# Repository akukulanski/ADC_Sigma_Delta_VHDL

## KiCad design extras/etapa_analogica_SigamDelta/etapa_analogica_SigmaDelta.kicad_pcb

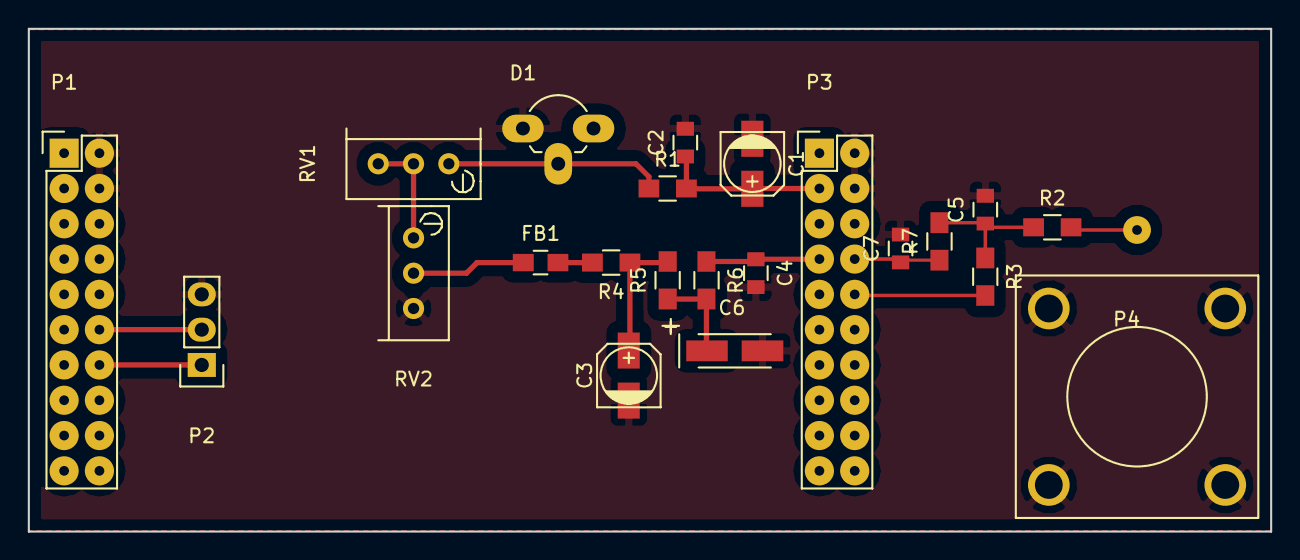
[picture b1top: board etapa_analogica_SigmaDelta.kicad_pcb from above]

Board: 2 copper layers, 89.4 x 36.2 mm, 22 parts (0 on the bottom side), 16 nets.

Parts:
C1, C3: 10u; c_elec_4x5.7
C2: 0,01u; C_0805
C4: 10u; C_0805
C5, C7: .1n; C_0805
C6: 10u; TantalC_SizeA_EIA-3216_HandSoldering
D1: LM336; TO-92_Rugged_Reverse
FB1: FILTER; C_0805_HandSoldering
P1, P3: CONN_02X10; Pin_Header_Straight_2x10
P2: CONN_01X03; Pin_Header_Straight_1x03
P4: BNC; chasis_bnc
R1: 560; R_0805_HandSoldering
R2, R3, R7: 150k; R_0805_HandSoldering
R4, R5, R6: 15k; R_0805_HandSoldering
RV1: 100; Potentiometer_Bourns_3296W_3-8Zoll_Inline_ScrewUp
RV2: 10k; Potentiometer_Bourns_3296W_3-8Zoll_Inline_ScrewUp

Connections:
/3,3v: C1.1, C2.1, P1.3, P3.3, R1.2
/5v: P1.1, P3.1
/N40: C4.1, P3.7, R6.1
/P35: P3.10, R3.2
/P41: C7.1, P3.8, R7.1
/Rx: P1.14, P2.1
/Tx: P1.12, P2.2
GND: C1.2, C2.2, C3.2, C4.2, C5.2, C6.2, C7.2, D1.1, P1.2, P1.4, P2.3, P3.2, P3.4, P4.2, RV2.3
unnamed: C3.1, R4.1, R5.2
unnamed: C5.1, R2.1, R3.1, R7.2
unnamed: C6.1, R5.1, R6.2
unnamed: D1.2, R1.1, RV1.1
unnamed: FB1.1, RV2.2
unnamed: FB1.2, R4.2
unnamed: P4.1, R2.2
unnamed: RV1.2, RV1.3, RV2.1

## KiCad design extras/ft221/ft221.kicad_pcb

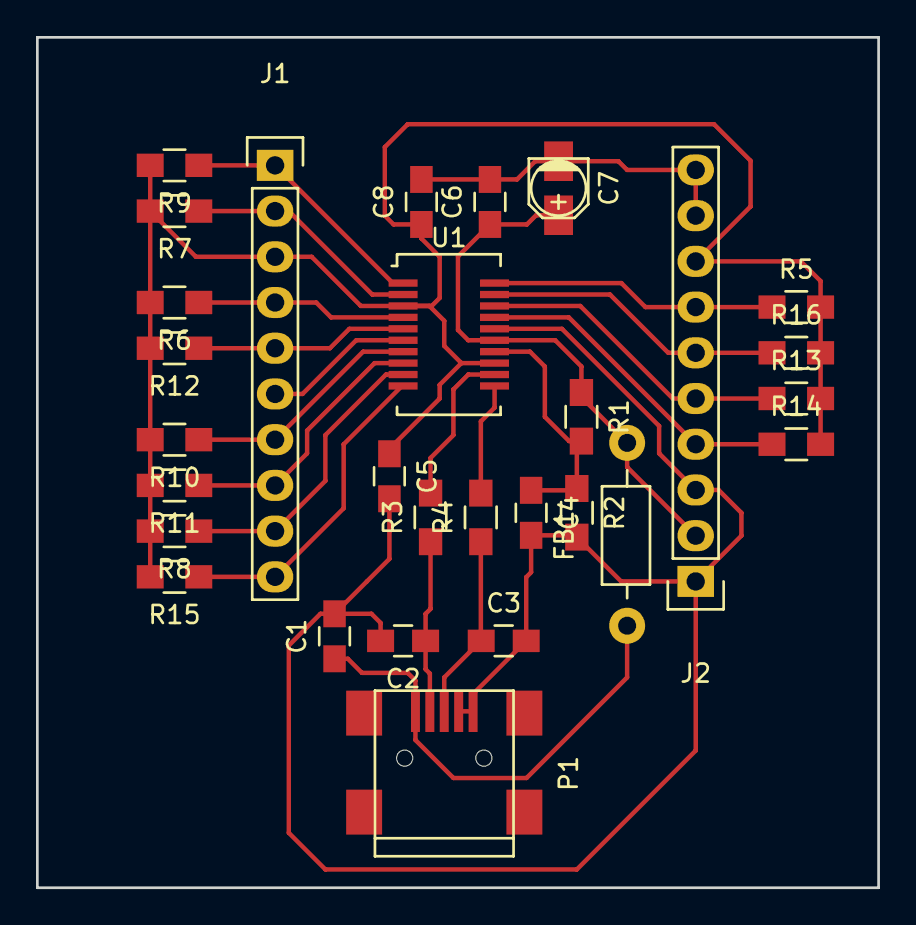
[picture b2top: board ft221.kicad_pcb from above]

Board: 2 copper layers, 46.7 x 47.2 mm, 29 parts (0 on the bottom side), 21 nets.

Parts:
C1, C4: 10n; C_0805_HandSoldering
C2, C3: 47p; C_0805_HandSoldering
C5, C6, C8: 0.1u; C_0805_HandSoldering
C7: 47u; c_elec_3x5.3
FB1: FILTER; Choke_Horizontal_RM10mm
J1, J2: SIL10; Pin_Header_Straight_1x10
P1: USB_B; USB_Mini-B
R1: 10k; R_0805_HandSoldering
R2: 15k; R_0805_HandSoldering
R3, R4: 27; R_0805_HandSoldering
R5, R6, R7, R8, R9, R10, R11, R12, R13, R14, R15, R16: 47k; R_0805_HandSoldering
U1: FT221; SSOP-20_5.99x8.66mm_Pitch0.635mm

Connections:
/CBUS3: J2.6, R16.1, U1.19
/CLK: J2.5, R13.1, U1.18
/CS#: J2.4, R14.1, U1.17
/IO0: J2.7, R5.1, U1.20
/IO1: J1.4, R6.1, U1.4
/IO2: J1.2, R7.1, U1.2
/IO3: J1.9, R8.1, U1.9
/IO4: J1.1, R9.1, U1.1
/IO5: J1.7, R10.1, U1.7
/IO6: J1.8, R11.1, U1.8
/IO7: J1.5, R12.1, U1.5
/MISO: J1.10, R15.1, U1.10
/VCCIO: C5.1, C8.1, J1.3, J2.8, R5.2, R6.2, R7.2, R8.2, R9.2, R10.2, R11.2, R12.2, R13.2, R14.2, R15.2, R16.2, U1.3, U1.13
GND: C1.2, C2.2, C3.2, C4.2, C5.2, C6.2, C7.2, C8.2, J1.6, J2.1, J2.3, J2.9, J2.10, P1.4, P1.5, R2.2, U1.6, U1.16
unnamed: C1.1, FB1.1, P1.1
unnamed: C2.1, P1.2, R3.1
unnamed: C3.1, P1.3, R4.1
unnamed: C4.1, R1.2, R2.1, U1.14
unnamed: R3.2, U1.12
unnamed: R4.2, U1.11
VCC: C6.1, C7.1, FB1.2, J2.2, R1.1, U1.15

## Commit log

2015-07-20 Commit inicial.
2015-07-21 Subiendo cic.vhd (falta bloque decimator y probar).
2015-07-21 Correcciones en el cic. Bloque decimador y su TB. Falta bufferear con F-F y TB del cic.
    Agregada funciton vectorize, para convertir
    std_logic a vector(0 downto 0)
    y no perder tiempo agregando signals.
2015-07-21 Buffereado con F-F los acumuladores a la salida, y los comb a la ent.
2015-07-21 Corregido los errores que mostraba la sintesis. Mirar los warnings.
2015-07-22 Subido archivos configuracion proyecto. Modificado cic (puesta a 0 señales no usadas) Puesto formato a los archivos.
2015-07-22 Corregido los truncamientos en cic. Falta un testbench completo.
2015-07-22 Combs, pasado a registrar la salida en vez de la entrada.
2015-07-23 Se agregan delayline y mac con preadder. No fueron probados. (igual no creo que esten mal, yo no tengo errores ajajaj)
2015-07-23 Se conecto output en preadd_mac
2015-07-23 Modificacion en RAM - Escritura en un ciclo de clock
2015-07-24 Test bench para ram. Cambiado nombre entity 'delay line' a 'ram'.
2015-07-24 Se agregan TB y fuentes de la generacion de punteros de ram. Se actualiza preaddmac para su correcto funcionamiento. DelayLine no funciona. Falta filtro FIR. Kuku se la come
2015-07-24 empezado el fir. modificación de ca2 previa a ram para multiplicación
2015-07-25 Cambiado todos los "add" que significaban "address" por "addr" para no confundir con las sumas.
2015-07-25 cambiando cosas
2015-07-25 Corregido address generator. Decrementa el contador 'cnt' en vez de incrementar.
2015-07-26 fir tb_ok.. revisar
2015-07-26 Se agrega testbench del CIC utilizando archivos (input stream de bits generado por Matlab)
2015-07-26 corregidas un par de cosas
2015-07-26 unificando2
2015-07-26 Corregida la ram. El multiplexor va ahí. Leer los comentarios. Implementado en block ram pero se lo cambia facil a distributed ram con un attribute (leer los comentarios!!!!!)
2015-07-26 Solucionado quilombo con push simultaneos mismo archivo.
2015-07-26 Ahi quedo corregido ram.vhd con los cambios antes mencionados
2015-07-26 un cambio chico en el fir
2015-07-26 Agregado dos generics para extender en signo y que reconozca el bloque mac con preadder dentro de un dsp. Los F-F de entrada se los puede llegar a sacar (igual los implementa dentro del dsp).
2015-07-26 cambio chico en fir y address_generator
2015-07-26 incorporación de cambios en mac al fir
2015-07-27 CIC corregido (decimador) - testbench anda ok! (sólo falta probar recortando bits :D)
2015-07-27 Cambiado decimator a algo que hace lo mismo pero escrito de mejor forma. Cambios menores: Sacado todas las tildes. Cambiado las ñ por n. Cambiados los integer por natural cuando eran anchos palabra.
2015-07-27 corrección en decimador
2015-07-27 eliminado el estado superfluo writing del address generator
2015-07-27 sacadas un par de líneas innecesarias
2015-07-27 agrego los scripts de vhdl
2015-07-27 Subido un package con los coeficientes. Hechas las modificaciones necesarias en el fir.
2015-07-28 Corregido scrip matlab,package y fir.
2015-07-28 Probado el fir. Correcciones menores hechas: - Cambiado (N_coeffs-1 downto 0) por (0 to N_coeffs-1) en coefficients.vhd - Agregada FF en lectura ROM(que esta dentro de la block-ram en realidad) para 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
2015-07-28 Sacados los when enable_mac_new_input = '1' else (others => '0') y extendido enable_mac_new_input hasta que se genere la salida. Conctado enable_mac_new_input a ce del preadd_mac.
2015-07-28 decimador sin retraso. renombro Coefficients.vhd por my_coeffs.vhd
2015-07-28 Ejemplo de lvds para instanciar en el top level
2015-07-28 Agrego archivos para comunicación serie
2015-07-29 Se agrega: - UART - Ejemplo de pll - top_level (solo del adc) - ad_uart (top_level + UART )
    Se mueve mytypes_pkg del archivo cic hacia la carpeta general CIC
2015-07-29 Verificado la respuesta al escalon fir con matlab (a mano, no exporte a archivo, sino compare valores).
2015-07-30 Cambios organiaztivos. Se cambia la esctructura de carpetas y se agrega un archivos de constantes. Quedan por cambiar algunas constantes de unos archivos todavia.
2015-07-30 Cambios menores
2015-07-30 programa para recibir por pto serie-OK!
2015-07-30 Separado totalmente las constantes del test_bench y de sintesis. Para esto agregado generic IS_TB y funciones decision. Para el futuro podriamos, calcular bits de cada etapa del cic en una funcion, y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
2015-07-30 Se agrega adc_uart.ucf
2015-09-03 Se modifico el CIC para que tenga logica de saturación positiva (no llegue al 100...000) y se hizo un testbench mediocre para probar su totalidad. Habria que hacer un TB mejor que exporte a matlab. E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
2015-09-08 Added: Synthesis, Place&Route and bitstreaming generator with makefile.
2015-09-10 BETA Release: TODO add a comunication for taking out the data
2015-09-11 Added: Uart (not tested)
2015-09-13 First Stable Realease: ADC(Clk 50M, Fs 28K) + UART 921600. Test over FPGA was realized.
2015-09-14 Vuelto para atras con la estupidez de las constantes. Cambiadas las listas de sensibilidad de uart que estaban mal (revisar). No pude simular por errores en mi ISE, después pruebo.
2015-09-18 Agregado kicad ft221 (dentro de extras)
2015-10-02 First stable revision- Its fucking working
2015-10-03 Se agrego simulacion de histeresis e independencias de R1,R2 y C
2015-10-04 Cambiado la ecuación recurrencia en el modulador sigma delta. Agregado filtro fir al final.
2015-10-04 Rx Uart added
2015-10-05 cosas_uart
2015-10-05 ordenando
2015-10-06 Arreglando el git
2015-10-11 Esquemático del modulador
2015-10-12 Mojo Cape edited
2015-10-13 Se agregan Rs en Vref. Se modifica R1
2015-10-13 Starting the layout
2015-10-13 Revert "Starting the layout"
    This reverts commit 84db6e4c9a3b0a09193008fcb0844fcb533dafef.
2015-10-13 Haciendo merge
2015-10-13 Se agrega R5, R6 al layout
2015-10-13 choque en filtro vref
2015-10-13 chasis bnc
2015-10-15 Cambiados capacitores filtro Vref por 10uF tantalio. Falta cambiar electrolítico de entrada.
2015-10-25 Agregado rooteo placa en Kicad
2015-10-29 Testing added: The fir is not workinggit push
2015-10-30 testbencheando con files,matlab,C...
2015-10-30 log, imagen. Script all.m más prolijo que los demás
2015-10-30 correcciones en simulaciones, cambios testbench
2015-10-30 cambios testbench (principalmente script all.m).
2015-10-31 tests
2015-10-31 correcciones testbenchs
2015-10-31 en branch por si edité alguna boludez en el vhdl mientras testeaba
2015-10-31 basura borrada
2015-11-01 Preparado todo para simular cic+fir
2015-11-01 emprolijados los scripts matlab para agilizar.
2015-11-01 Se agrega instanciación del fir más la uart
2015-11-01 Simulacion cic+fir, ejecutar ultima section all.m
2015-11-01 ordenado
2015-11-01 uart recibe ok p/ fir.
2015-11-01 mas tests
2015-11-01 new_decimator
2015-11-01 fir registrando entradas!
2015-11-01 pauno_cosas
2015-11-01 SOLVEEEEEEEEEEEEED!!!
2015-11-01 imagen}
2015-11-01 Puesto el FIR que ecualiza, funciona perfecto
2015-11-02 Imagenes con el FIR de ecualización
2015-11-02 Mejorado ADC simulation
2015-12-03 STABLE
2015-12-03 Agregado Paper y algunas simulaciones
2015-12-03 correcciones paper
2015-12-03 Algunas correcciones ortográficas
2015-12-06 Modificado Paper. Cambiado en fir.vhd operaciones para llegar a plena escala asi no infiere un DSP48A1. Modificaciones en simulaciones para sacar imagenes.
2015-12-06 Mi ultima correccion del paper
2015-12-07 Demski Reviso el paper
2015-12-07 .tex added
2015-12-07 Fixed: imagen tiempo continuo
2015-12-07 Actualizada imagenes bien exportadas desde matlab
2015-12-07 Revisión del paper.
2015-12-07 Correciones
2015-12-07 Correciones de Ivan. Falta el mas,menos en el LVDS
2015-12-07 Algunas correcciones que mencionó Andy y agregado de CONECTORES en los textos de las imágenes
2015-12-07 Cambios paper
2015-12-07 Formateando
2015-12-07 Todas las imagenes son nuestras
2015-12-07 Corregido error formula (18)
2016-04-10 Comenzando traducción paper
